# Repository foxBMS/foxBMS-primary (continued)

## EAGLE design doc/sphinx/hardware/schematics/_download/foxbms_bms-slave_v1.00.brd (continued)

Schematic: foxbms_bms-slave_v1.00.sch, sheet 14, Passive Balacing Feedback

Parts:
C1401, C1402: 1uF, 20%, 16V; 0603
IC1401, IC1402, IC1403, IC1404, IC1405, IC1406, IC1407, IC1408, IC1409, IC1410, IC1411, IC1412: CPC1008N; K_SMD_SOP-4_R_IXYS_REV01
M1401, M1402: LTC1380CGN; IC_SMD_SSOP-16_(GN16)_R_LINEAR_REV01
R1401, R1402, R1403, R1404, R1405, R1406, R1408, R1409, R1410, R1411, R1412, R1413: 130, 10%, 1/10W; 0603
R1407: 1k, 10%, 1/10W; 0603
R1414, R1415, R1416, R1417, R1418, R1419, R1420, R1421, R1422, R1423, R1424, R1425, R1426, R1427, R1428, R1429: 10k, 10%, 1/10W; 0603

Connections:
+5.0V_VREG_1: C1401.2, C1402.2, M1401.12 (A1), M1401.16 (VCC), M1402.12 (A1), M1402.13 (A0), M1402.16 (VCC), R1407.1; also elsewhere on the board
CELL0_FEEDBACK: IC1406.3, M1401.1 (S0), R1414.1
CELL0_FEEDBACK+: R1406.2; also elsewhere on the board
CELL1_FEEDBACK: IC1405.3, M1401.2 (S1), R1415.1
CELL1_FEEDBACK+: R1405.2; also elsewhere on the board
CELL2_FEEDBACK: IC1404.3, M1401.3 (S2), R1416.1
CELL2_FEEDBACK+: R1404.2; also elsewhere on the board
CELL3_FEEDBACK: IC1403.3, M1401.4 (S3), R1417.1
CELL3_FEEDBACK+: R1403.2; also elsewhere on the board
CELL4_FEEDBACK: IC1402.3, M1401.5 (S4), R1418.1
CELL4_FEEDBACK+: R1402.2; also elsewhere on the board
CELL5_FEEDBACK: IC1401.3, M1401.6 (S5), R1419.1
CELL5_FEEDBACK+: R1401.2; also elsewhere on the board
CELL6_FEEDBACK: IC1412.3, M1401.7 (S6), R1420.1
CELL6_FEEDBACK+: R1413.2; also elsewhere on the board
CELL7_FEEDBACK: IC1411.3, M1401.8 (S7), R1421.1
CELL7_FEEDBACK+: R1412.2; also elsewhere on the board
CELL8_FEEDBACK: IC1410.3, M1402.1 (S0), R1422.1
CELL8_FEEDBACK+: R1411.2; also elsewhere on the board
CELL9_FEEDBACK: IC1409.3, M1402.2 (S1), R1423.1
CELL9_FEEDBACK+: R1410.2; also elsewhere on the board
CELL10_FEEDBACK: IC1408.3, M1402.3 (S2), R1424.1
CELL10_FEEDBACK+: R1409.2; also elsewhere on the board
CELL11_FEEDBACK: IC1407.3, M1402.4 (S3), R1425.1
CELL11_FEEDBACK+: R1408.2; also elsewhere on the board
FUSED_CELL_0+: IC1405.2 (CON-); also elsewhere on the board
FUSED_CELL_1+: IC1404.2 (CON-); also elsewhere on the board
FUSED_CELL_2+: IC1403.2 (CON-); also elsewhere on the board
FUSED_CELL_3+: IC1402.2 (CON-); also elsewhere on the board
FUSED_CELL_4+: IC1401.2 (CON-); also elsewhere on the board
FUSED_CELL_5+: IC1412.2 (CON-); also elsewhere on the board
FUSED_CELL_6+: IC1411.2 (CON-); also elsewhere on the board
FUSED_CELL_7+: IC1410.2 (CON-); also elsewhere on the board
FUSED_CELL_8+: IC1409.2 (CON-); also elsewhere on the board
FUSED_CELL_9+: IC1408.2 (CON-); also elsewhere on the board
FUSED_CELL_10+: IC1407.2 (CON-); also elsewhere on the board
FUSED_VBAT-: C1401.1, C1402.1, IC1406.2 (CON-), M1401.10 (VEE), M1401.11 (GND), M1401.13 (A0), M1402.10 (VEE), M1402.11 (GND), R1414.2, R1415.2, R1416.2, R1417.2, R1418.2, R1419.2, R1420.2, R1421.2, R1422.2, R1423.2, R1424.2, R1425.2, R1426.2, R1427.2, R1428.2, R1429.2; also elsewhere on the board
unnamed: IC1401.4, IC1402.4, IC1403.4, IC1404.4, IC1405.4, IC1406.4, IC1407.4, IC1408.4, IC1409.4, IC1410.4, IC1411.4, IC1412.4, R1407.2
unnamed: IC1402.1 (CON+), R1402.1
unnamed: IC1403.1 (CON+), R1403.1
unnamed: IC1404.1 (CON+), R1404.1
unnamed: IC1408.1 (CON+), R1409.1
unnamed: IC1409.1 (CON+), R1410.1
unnamed: IC1405.1 (CON+), R1405.1
unnamed: IC1407.1 (CON+), R1408.1
unnamed: IC1410.1 (CON+), R1411.1
unnamed: IC1411.1 (CON+), R1412.1
unnamed: IC1406.1 (CON+), R1406.1
unnamed: IC1412.1 (CON+), R1413.1
unnamed: IC1401.1 (CON+), R1401.1
SECONDARY-OPA_IN: M1401.9 (DO), M1402.9 (DO); also elsewhere on the board
SECONDARY-SCL: M1401.15 (SCL), M1402.15 (SCL); also elsewhere on the board
SECONDARY-SDA: M1401.14 (SDA), M1402.14 (SDA); also elsewhere on the board
SECONDARY_D/A_INPUT_0: M1402.5 (S4), R1426.1; also elsewhere on the board
SECONDARY_D/A_INPUT_1: M1402.6 (S5), R1427.1; also elsewhere on the board
SECONDARY_D/A_INPUT_2: M1402.7 (S6), R1428.1; also elsewhere on the board
SECONDARY_D/A_INPUT_3: M1402.8 (S7), R1429.1; also elsewhere on the board

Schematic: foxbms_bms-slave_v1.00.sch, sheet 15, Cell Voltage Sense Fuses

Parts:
F1501, F1515: 0.5A, 63V, 0.25R; 1206
F1502, F1503, F1504, F1505, F1506, F1507, F1508, F1509, F1510, F1511, F1512, F1513, F1514: FUSE: 0.250A, 32V, 0.57R; 0603
LSP1501, LSP1502, LSP1503, LSP1504, LSP1505, LSP1506, LSP1507, LSP1508, LSP1509, LSP1510, LSP1511, LSP1512, LSP1513, LSP1514, LSP1515: PAD_2.0X1.5MM; PAD2.0X1.5MM
SJ1501, SJ1502: SJ

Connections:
CELL_0+: F1503.1; also elsewhere on the board
CELL_0-: F1502.1, SJ1501.1; also elsewhere on the board
CELL_1+: F1504.1; also elsewhere on the board
CELL_2+: F1505.1; also elsewhere on the board
CELL_3+: F1506.1; also elsewhere on the board
CELL_4+: F1507.1; also elsewhere on the board
CELL_5+: F1508.1; also elsewhere on the board
CELL_6+: F1509.1; also elsewhere on the board
CELL_7+: F1510.1; also elsewhere on the board
CELL_8+: F1511.1; also elsewhere on the board
CELL_9+: F1512.1; also elsewhere on the board
CELL_10+: F1513.1; also elsewhere on the board
CELL_11+: F1514.1, SJ1502.2; also elsewhere on the board
FUSED_CELL_0+: F1503.2, LSP1503.P$1; also elsewhere on the board
FUSED_CELL_0-: F1502.2, LSP1502.P$1; also elsewhere on the board
FUSED_CELL_1+: F1504.2, LSP1504.P$1; also elsewhere on the board
FUSED_CELL_2+: F1505.2, LSP1505.P$1; also elsewhere on the board
FUSED_CELL_3+: F1506.2, LSP1506.P$1; also elsewhere on the board
FUSED_CELL_4+: F1507.2, LSP1507.P$1; also elsewhere on the board
FUSED_CELL_5+: F1508.2, LSP1508.P$1; also elsewhere on the board
FUSED_CELL_6+: F1509.2, LSP1509.P$1; also elsewhere on the board
FUSED_CELL_7+: F1510.2, LSP1510.P$1; also elsewhere on the board
FUSED_CELL_8+: F1511.2, LSP1511.P$1; also elsewhere on the board
FUSED_CELL_9+: F1512.2, LSP1512.P$1; also elsewhere on the board
FUSED_CELL_10+: F1513.2, LSP1513.P$1; also elsewhere on the board
FUSED_CELL_11+: F1514.2, LSP1514.P$1; also elsewhere on the board
FUSED_VBAT+: F1515.2, LSP1515.P$1; also elsewhere on the board
FUSED_VBAT-: F1501.2, LSP1501.P$1; also elsewhere on the board
VBAT+: F1515.1, SJ1502.1; also elsewhere on the board
VBAT-: F1501.1, SJ1501.2; also elsewhere on the board

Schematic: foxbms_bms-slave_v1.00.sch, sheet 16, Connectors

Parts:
X1601, X1602: 43045-0406_MOLEX_4PIN; X_SMD_MOLEX_43045-0408_R_REV01
X1603: 43045-1606_MOLEX_16PIN; X_SMD_MOLEX_43045-1608_R_REV01
X1604, X1607, X1608: MA10-2
X1605: MA09-2
X1606: 43045-2406_MOLEX_24PIN; X_SMD_MOLEX_43045-2408_R_REV01

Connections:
+3.0V_VREF2_0: X1604.18; also elsewhere on the board
+3.0V_VREF2_1: X1604.17; also elsewhere on the board
+5.0V_VREG_0: X1604.16; also elsewhere on the board
+5.0V_VREG_1: X1604.15; also elsewhere on the board
CELL_0+: X1603.2; also elsewhere on the board
CELL_0-: X1603.9; also elsewhere on the board
CELL_1+: X1603.10; also elsewhere on the board
CELL_2+: X1603.3; also elsewhere on the board
CELL_3+: X1603.11; also elsewhere on the board
CELL_4+: X1603.4; also elsewhere on the board
CELL_5+: X1603.12; also elsewhere on the board
CELL_6+: X1603.5; also elsewhere on the board
CELL_7+: X1603.13; also elsewhere on the board
CELL_8+: X1603.6; also elsewhere on the board
CELL_9+: X1603.14; also elsewhere on the board
CELL_10+: X1603.7; also elsewhere on the board
CELL_11+: X1603.15; also elsewhere on the board
FUSED_VBAT-: X1605.17, X1605.18, X1606.1, X1606.2, X1606.3, X1606.4, X1606.5, X1606.6, X1606.7, X1606.8, X1606.9, X1606.10, X1606.11, X1606.12, X1607.2, X1607.4, X1607.6, X1607.8, X1607.10, X1607.12, X1607.14, X1607.16, X1607.18, X1607.20, X1608.2, X1608.4, X1608.6, X1608.8, X1608.10, X1608.12, X1608.14, X1608.16, X1608.18, X1608.20; also elsewhere on the board
PRIMARY-GPIO0-OPT: X1604.6; also elsewhere on the board
PRIMARY-GPIO1: X1604.8; also elsewhere on the board
PRIMARY-GPIO2: X1604.10; also elsewhere on the board
PRIMARY-GPIO3-OPT: X1604.12; also elsewhere on the board
PRIMARY-GPIO4-OPT: X1604.14; also elsewhere on the board
PRIMARY-IN+_P: X1601.1; also elsewhere on the board
PRIMARY-IN-_N: X1601.3; also elsewhere on the board
PRIMARY-OUT+_P: X1601.4; also elsewhere on the board
PRIMARY-OUT-_N: X1601.2; also elsewhere on the board
PRIMARY-WDT: X1604.20; also elsewhere on the board
PRIMARY_D/A_INPUT_0: X1605.1; also elsewhere on the board
PRIMARY_D/A_INPUT_1: X1605.2; also elsewhere on the board
PRIMARY_D/A_INPUT_2: X1605.3; also elsewhere on the board
PRIMARY_D/A_INPUT_3: X1605.4; also elsewhere on the board
PRIMARY_D/A_INPUT_4: X1605.5; also elsewhere on the board
PRIMARY_D/A_INPUT_5: X1605.6; also elsewhere on the board
PRIMARY_D/A_INPUT_6: X1605.7; also elsewhere on the board
PRIMARY_D/A_INPUT_7: X1605.8; also elsewhere on the board
PRIMARY_D/A_INPUT_8: X1605.9; also elsewhere on the board
PRIMARY_D/A_INPUT_9: X1605.10; also elsewhere on the board
PRIMARY_D/A_INPUT_10: X1605.11; also elsewhere on the board
PRIMARY_D/A_INPUT_11: X1605.12; also elsewhere on the board
PRIMARY_D/A_INPUT_12: X1605.13; also elsewhere on the board
PRIMARY_D/A_INPUT_13: X1605.14; also elsewhere on the board
PRIMARY_D/A_INPUT_14: X1605.15; also elsewhere on the board
PRIMARY_D/A_INPUT_15: X1605.16; also elsewhere on the board
SECONDARY-GPIO0-OPT: X1604.5; also elsewhere on the board
SECONDARY-GPIO1: X1604.7; also elsewhere on the board
SECONDARY-GPIO2: X1604.9; also elsewhere on the board
SECONDARY-GPIO3-OPT: X1604.11; also elsewhere on the board
SECONDARY-GPIO4-OPT: X1604.13; also elsewhere on the board
SECONDARY-IN+_P: X1602.1; also elsewhere on the board
SECONDARY-IN-_N: X1602.3; also elsewhere on the board
SECONDARY-OUT+_P: X1602.4; also elsewhere on the board
SECONDARY-OUT-_N: X1602.2; also elsewhere on the board
SECONDARY-WDT: X1604.19; also elsewhere on the board
SECONDARY_D/A_INPUT_0: X1604.1; also elsewhere on the board
SECONDARY_D/A_INPUT_1: X1604.2; also elsewhere on the board
SECONDARY_D/A_INPUT_2: X1604.3; also elsewhere on the board
SECONDARY_D/A_INPUT_3: X1604.4; also elsewhere on the board
T-SENSOR_0: X1606.24; also elsewhere on the board
T-SENSOR_1: X1606.23; also elsewhere on the board
T-SENSOR_2: X1606.22; also elsewhere on the board
T-SENSOR_3: X1606.21; also elsewhere on the board
T-SENSOR_4: X1606.20; also elsewhere on the board
T-SENSOR_5: X1606.19; also elsewhere on the board
T-SENSOR_6: X1607.1; also elsewhere on the board
T-SENSOR_7: X1607.3; also elsewhere on the board
T-SENSOR_8: X1607.5; also elsewhere on the board
T-SENSOR_9: X1607.7; also elsewhere on the board
T-SENSOR_10: X1607.9; also elsewhere on the board
T-SENSOR_11: X1607.11; also elsewhere on the board
T-SENSOR_12: X1607.13; also elsewhere on the board
T-SENSOR_13: X1607.15; also elsewhere on the board
T-SENSOR_14: X1607.17; also elsewhere on the board
T-SENSOR_15: X1607.19; also elsewhere on the board
T-SENSOR_16: X1606.18; also elsewhere on the board
T-SENSOR_17: X1606.17; also elsewhere on the board
T-SENSOR_18: X1606.16; also elsewhere on the board
T-SENSOR_19: X1606.15; also elsewhere on the board
T-SENSOR_20: X1606.14; also elsewhere on the board
T-SENSOR_21: X1606.13; also elsewhere on the board
T-SENSOR_22: X1608.19; also elsewhere on the board
T-SENSOR_23: X1608.17; also elsewhere on the board
T-SENSOR_24: X1608.15; also elsewhere on the board
T-SENSOR_25: X1608.13; also elsewhere on the board
T-SENSOR_26: X1608.11; also elsewhere on the board
T-SENSOR_27: X1608.9; also elsewhere on the board
T-SENSOR_28: X1608.7; also elsewhere on the board
T-SENSOR_29: X1608.5; also elsewhere on the board
T-SENSOR_30: X1608.3; also elsewhere on the board
T-SENSOR_31: X1608.1; also elsewhere on the board
VBAT+: X1603.16; also elsewhere on the board
VBAT-: X1603.1; also elsewhere on the board

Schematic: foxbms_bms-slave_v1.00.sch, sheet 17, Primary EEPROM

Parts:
C1701: 100nF, 20%, 16V; 0603
IC1701: 24AA02UID; IC_SMD_SOT23-5_R_MICROCHIP_REV01

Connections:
+5.0V_VREG_0: C1701.2, IC1701.4 (VCC); also elsewhere on the board
FUSED_VBAT-: C1701.1, IC1701.2 (VSS); also elsewhere on the board
PRIMARY-SCL: IC1701.1 (SCL); also elsewhere on the board
PRIMARY-SDA: IC1701.3 (SDA); also elsewhere on the board

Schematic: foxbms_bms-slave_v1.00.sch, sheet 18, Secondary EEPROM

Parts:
C1801: 100nF, 20%, 16V; 0603
IC1801: 24AA02UID; IC_SMD_SOT23-5_R_MICROCHIP_REV01

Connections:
+5.0V_VREG_1: C1801.2, IC1801.4 (VCC); also elsewhere on the board
FUSED_VBAT-: C1801.1, IC1801.2 (VSS); also elsewhere on the board
SECONDARY-SCL: IC1801.1 (SCL); also elsewhere on the board
SECONDARY-SDA: IC1801.3 (SDA); also elsewhere on the board

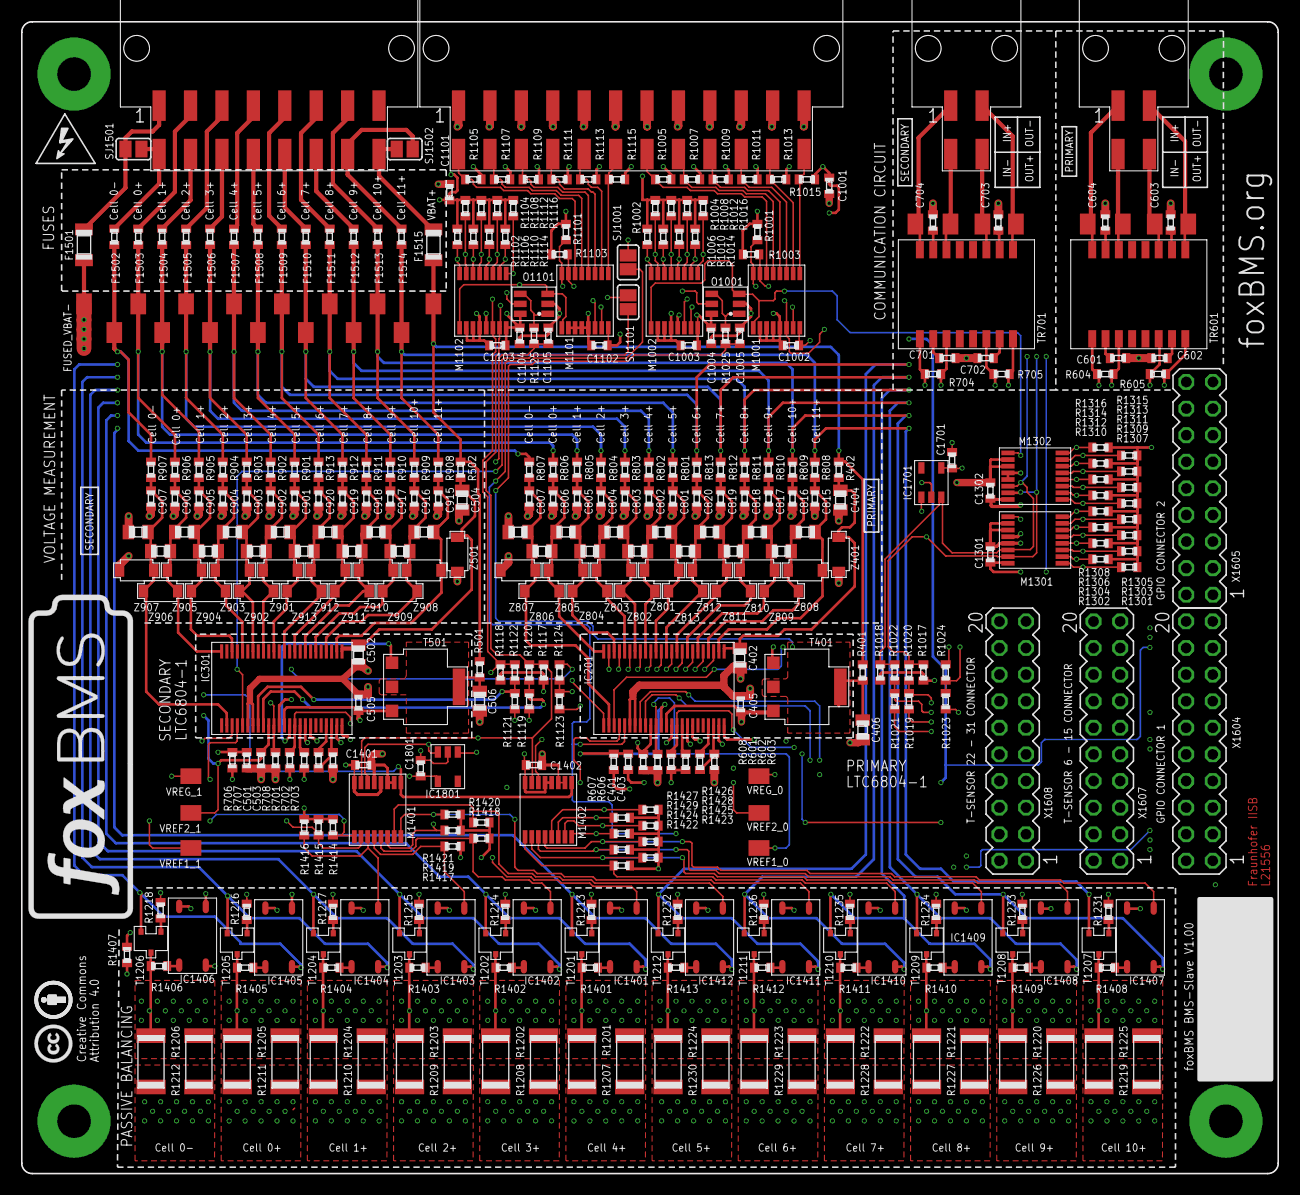
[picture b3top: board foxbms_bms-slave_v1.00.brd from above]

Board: 6 copper layers, 120.0 x 110.0 mm, 391 parts (0 on the bottom side), 244 nets.

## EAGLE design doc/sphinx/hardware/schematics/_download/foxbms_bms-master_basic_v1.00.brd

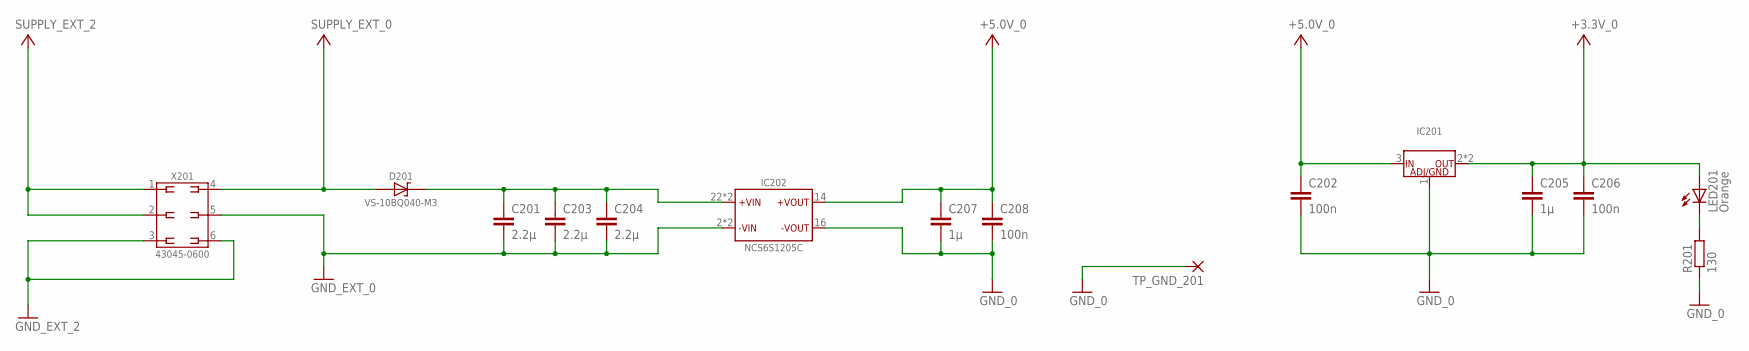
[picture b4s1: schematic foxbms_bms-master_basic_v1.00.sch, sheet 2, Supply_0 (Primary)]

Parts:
C201, C203, C204: 2.2µ; C0805
C202, C206, C208: 100n; C0603
C205, C207: 1µ; C0603
D201: VS-10BQ040-M3; D_SMD_SMB_(DO-214AA)_R_VISHAY_REV01
IC201: LM1085IS-5.0/NOPB; IC_SMD_TO-263-3_(KTT0003B)_R_TI_REV01
IC202: MURATA_NCS6S1205C; IC_TH_32,00MMX20,00MMX10,00MM_(7-PIN)_R_MURATA_REV01
LED201: Orange; CHIP-LED0603
R201: 130; R0603
TP_GND_201: 1,6/0,8
X201: 43045-0600_MOLEX_6PIN; X_TH_MOLEX_43045-0600_R_REV01

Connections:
+3.3V_0: C205.1, C206.1, IC201.2 (OUT), IC201.4 (OUT), LED201.A; also elsewhere on the board
+5.0V_0: C202.1, C207.1, C208.1, IC201.3 (IN), IC202.14 (+VOUT); also elsewhere on the board
GND_0: C202.2, C205.2, C206.2, C207.2, C208.2, IC201.1 (ADJ/GND), IC202.16 (-VOUT), R201.1, TP_GND_201.1; also elsewhere on the board
GND_EXT_0: C201.2, C203.2, C204.2, IC202.2 (-VIN), IC202.3 (-VIN), X201.5; also elsewhere on the board
GND_EXT_2: X201.3, X201.6; also elsewhere on the board
unnamed: LED201.C, R201.2
unnamed: C201.1, C203.1, C204.1, D201.C, IC202.22 (+VIN), IC202.23 (+VIN)
SUPPLY_EXT_0: D201.A, X201.4; also elsewhere on the board
SUPPLY_EXT_2: X201.1, X201.2; also elsewhere on the board

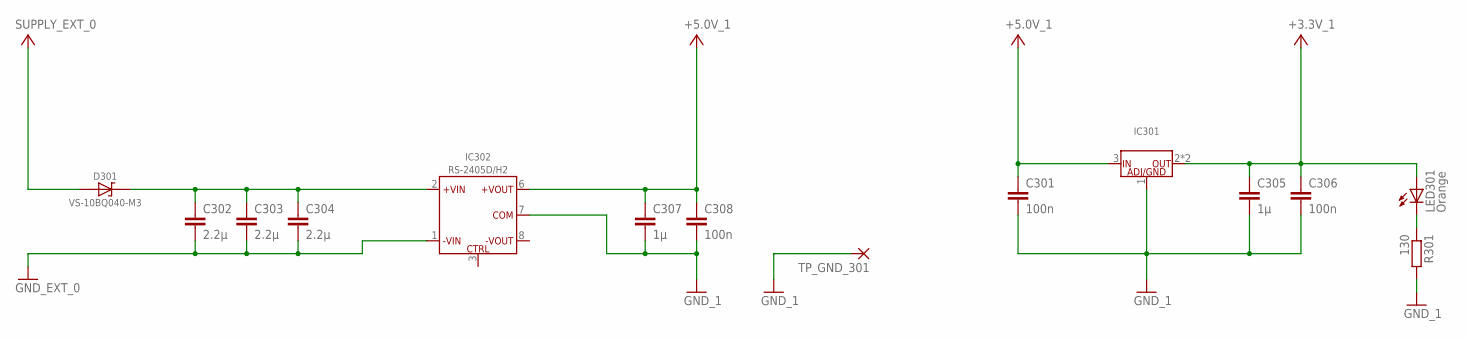
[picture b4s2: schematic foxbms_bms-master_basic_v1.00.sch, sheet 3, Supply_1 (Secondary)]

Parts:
C301, C306, C308: 100n; C0603
C302, C303, C304: 2.2µ; C0805
C305, C307: 1µ; C0603
D301: VS-10BQ040-M3; D_SMD_SMB_(DO-214AA)_R_VISHAY_REV01
IC301: LM1085IS-5.0/NOPB; IC_SMD_TO-263-3_(KTT0003B)_R_TI_REV01
IC302: RS-2405D/H2; IC_TH_SIP8_R_RECOM_REV01
LED301: Orange; CHIP-LED0603
R301: 130; R0603
TP_GND_301: 1,6/0,8

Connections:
+3.3V_1: C305.1, C306.1, IC301.2 (OUT), IC301.4 (OUT), LED301.A; also elsewhere on the board
+5.0V_1: C301.1, C307.1, C308.1, IC301.3 (IN), IC302.6 (+VOUT); also elsewhere on the board
GND_1: C301.2, C305.2, C306.2, C307.2, C308.2, IC301.1 (ADJ/GND), IC302.7 (COM), R301.2, TP_GND_301.1; also elsewhere on the board
GND_EXT_0: C302.2, C303.2, C304.2, IC302.1 (-VIN); also elsewhere on the board
unnamed: LED301.C, R301.1
unnamed: C302.1, C303.1, C304.1, D301.C, IC302.2 (+VIN)
SUPPLY_EXT_0: D301.A; also elsewhere on the board

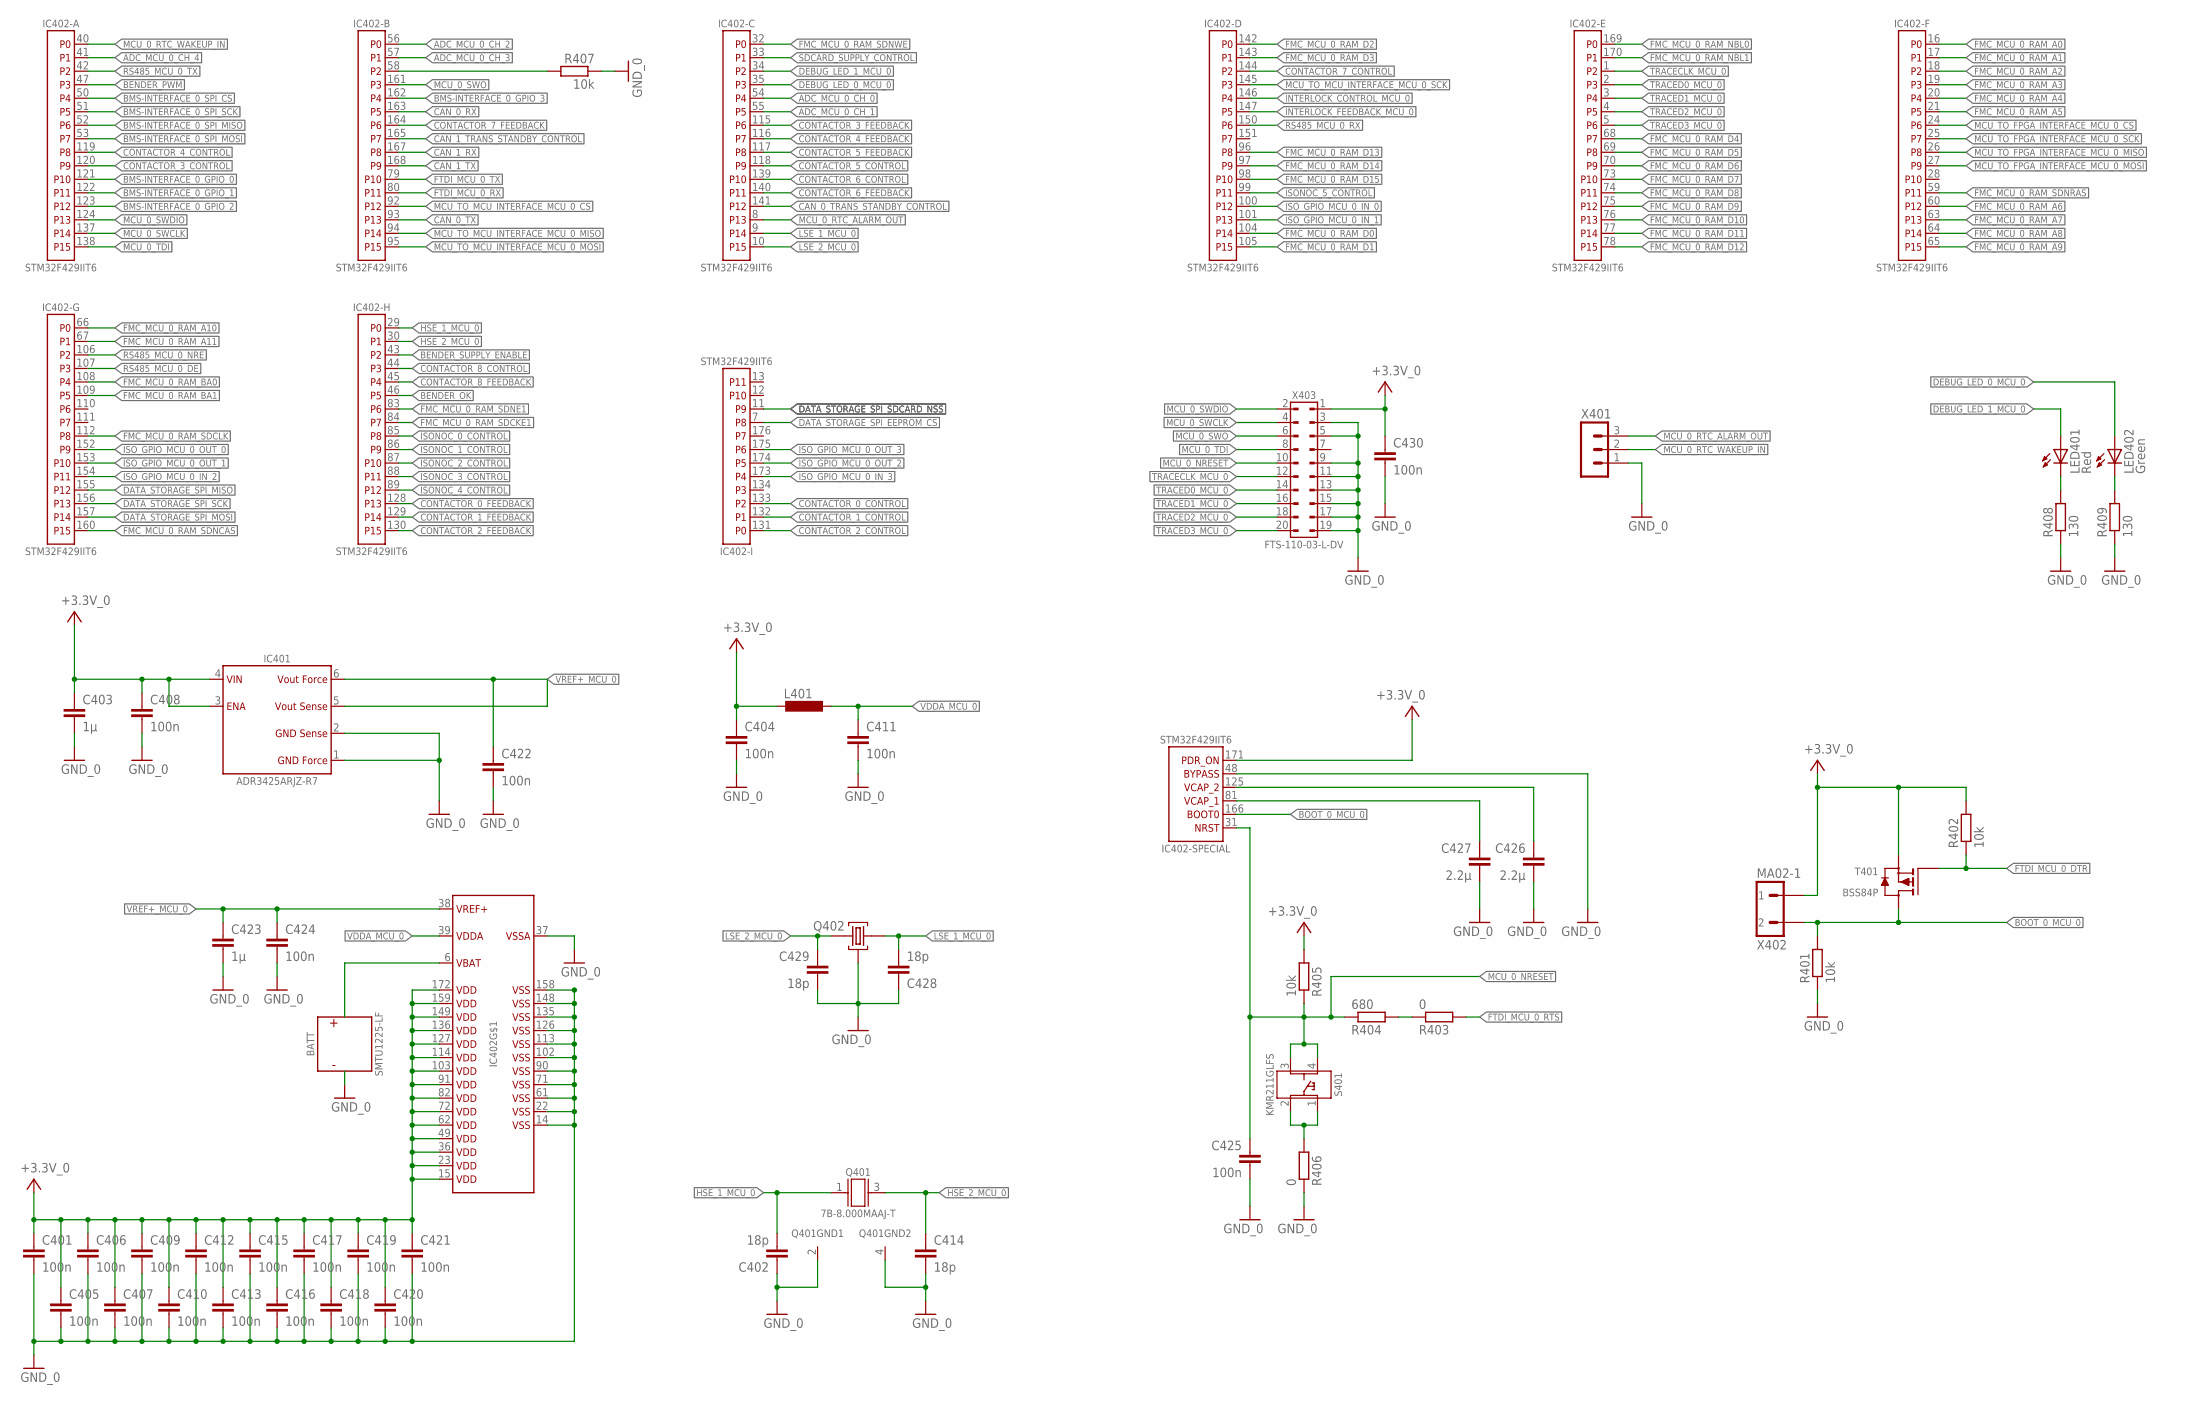
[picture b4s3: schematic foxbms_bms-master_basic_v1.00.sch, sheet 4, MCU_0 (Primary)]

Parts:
BATT: SMTU1225-LF; X_SMD_(23,70MM_X_12,70MM_X_5,00MM)_R_RENATA_REV01
C401, C404, C405, C406, C407, C408, C409, C410, C411, C412, C413, C415, C416, C417, C418, C419, C420, C421, C422, C424, C425, C430: 100n; C0603
C402, C414, C428, C429: 18p; C0603
C403, C423: 1µ; C0603
C426, C427: 2.2µ; C0603
IC401: ADR3425ARJZ; IC_SMD_SOT23-6_(MO-178-AB)_R_AD_REV01
IC402: STM32F429IIT6; IC_SMD_LQFP176_R_ST_REV01
L401: L0805; 0805
LED401: Red; CHIP-LED0603
LED402: Green; CHIP-LED0603
Q401: 7B-8.000MAAJ-T; G_SMD_5,00MM_X_3,20MM_0,90MM_(7B)_TXC_REV01
Q402: MS3V; MS3V-T1R
R401, R402, R405, R407: 10k; R0603
R403, R406: 0; R0603
R404: 680; R0603
R408, R409: 130; R0603
S401: KMR211GLFS; S_SMD_4,60MMX2,80MMX1,90MM_R_CK-COMPONENTS_REV01
T401: BSS84P; V_SMD_SOT23_(TO-236AB)_R_INFINEON_REV01
X401: MA03-1
X402: MA02-1
X403: SAMTEC_FTS_20POL_HEADER_VERTIKAL_REV01; X_SMD_FTS_110-03_(20POL)_R_SAMTEC_REV01

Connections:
+3.3V_0: C401.1, C403.1, C404.1, C405.1, C406.1, C407.1, C408.1, C409.1, C410.1, C412.1, C413.1, C415.1, C416.1, C417.1, C418.1, C419.1, C420.1, C421.1, C430.1, IC401.3 (ENABLE), IC401.4 (VIN), IC402.15 (VDD1), IC402.23 (VDD2), IC402.36 (VDD3), IC402.49 (VDD4), IC402.62 (VDD5), IC402.72 (VDD6), IC402.82 (VDD7), IC402.91 (VDD8), IC402.103 (VDD9), IC402.114 (VDD10), IC402.127 (VDD11), IC402.136 (VDD12), IC402.149 (VDD13), IC402.159 (VDD14), IC402.171 (PDR_ON), IC402.172 (VDD15), L401.1, R402.2, R405.2, T401.2 (S), X402.1, X403.1; also elsewhere on the board
ADC_MCU_0_CH_0: IC402.54 (P4); also elsewhere on the board
ADC_MCU_0_CH_1: IC402.55 (P5); also elsewhere on the board
ADC_MCU_0_CH_2: IC402.56 (P0); also elsewhere on the board
ADC_MCU_0_CH_3: IC402.57 (P1); also elsewhere on the board
ADC_MCU_0_CH_4: IC402.41 (P1); also elsewhere on the board
BENDER_OK: IC402.46 (P5); also elsewhere on the board
BENDER_PWM: IC402.47 (P3); also elsewhere on the board
BENDER_SUPPLY_ENABLE: IC402.43 (P2); also elsewhere on the board
BMS-INTERFACE_0_GPIO_0: IC402.121 (P10); also elsewhere on the board
BMS-INTERFACE_0_GPIO_1: IC402.122 (P11); also elsewhere on the board
BMS-INTERFACE_0_GPIO_2: IC402.123 (P12); also elsewhere on the board
BMS-INTERFACE_0_GPIO_3: IC402.162 (P4); also elsewhere on the board
BMS-INTERFACE_0_SPI_CS: IC402.50 (P4); also elsewhere on the board
BMS-INTERFACE_0_SPI_MISO: IC402.52 (P6); also elsewhere on the board
BMS-INTERFACE_0_SPI_MOSI: IC402.53 (P7); also elsewhere on the board
BMS-INTERFACE_0_SPI_SCK: IC402.51 (P5); also elsewhere on the board
BOOT_0_MCU_0: IC402.166 (BOOT0), R401.2, T401.3 (D), X402.2
CAN_0_RX: IC402.163 (P5); also elsewhere on the board
CAN_0_TRANS_STANDBY_CONTROL: IC402.141 (P12); also elsewhere on the board
CAN_0_TX: IC402.93 (P13); also elsewhere on the board
CAN_1_RX: IC402.167 (P8); also elsewhere on the board
CAN_1_TRANS_STANDBY_CONTROL: IC402.165 (P7); also elsewhere on the board
CAN_1_TX: IC402.168 (P9); also elsewhere on the board
CONTACTOR_0_CONTROL: IC402.133 (P2); also elsewhere on the board
CONTACTOR_0_FEEDBACK: IC402.128 (P13); also elsewhere on the board
CONTACTOR_1_CONTROL: IC402.132 (P1); also elsewhere on the board
CONTACTOR_1_FEEDBACK: IC402.129 (P14); also elsewhere on the board
CONTACTOR_2_CONTROL: IC402.131 (P0); also elsewhere on the board
CONTACTOR_2_FEEDBACK: IC402.130 (P15); also elsewhere on the board
CONTACTOR_3_CONTROL: IC402.120 (P9); also elsewhere on the board
CONTACTOR_3_FEEDBACK: IC402.115 (P6); also elsewhere on the board
CONTACTOR_4_CONTROL: IC402.119 (P8); also elsewhere on the board
CONTACTOR_4_FEEDBACK: IC402.116 (P7); also elsewhere on the board
CONTACTOR_5_CONTROL: IC402.118 (P9); also elsewhere on the board
CONTACTOR_5_FEEDBACK: IC402.117 (P8); also elsewhere on the board
CONTACTOR_6_CONTROL: IC402.139 (P10); also elsewhere on the board
CONTACTOR_6_FEEDBACK: IC402.140 (P11); also elsewhere on the board
CONTACTOR_7_CONTROL: IC402.144 (P2); also elsewhere on the board
CONTACTOR_7_FEEDBACK: IC402.164 (P6); also elsewhere on the board
CONTACTOR_8_CONTROL: IC402.44 (P3); also elsewhere on the board
CONTACTOR_8_FEEDBACK: IC402.45 (P4); also elsewhere on the board
DATA_STORAGE_SPI_EEPROM_CS: IC402.7 (P8); also elsewhere on the board
DATA_STORAGE_SPI_MISO: IC402.155 (P12); also elsewhere on the board
DATA_STORAGE_SPI_MOSI: IC402.157 (P14); also elsewhere on the board
DATA_STORAGE_SPI_SCK: IC402.156 (P13); also elsewhere on the board
DATA_STORAGE_SPI_SDCARD_NSS: IC402.11 (P9); also elsewhere on the board
DEBUG_LED_0_MCU_0: IC402.35 (P3), LED402.A
DEBUG_LED_1_MCU_0: IC402.34 (P2), LED401.A
FMC_MCU_0_RAM_A0: IC402.16 (P0); also elsewhere on the board
FMC_MCU_0_RAM_A1: IC402.17 (P1); also elsewhere on the board
FMC_MCU_0_RAM_A2: IC402.18 (P2); also elsewhere on the board
FMC_MCU_0_RAM_A3: IC402.19 (P3); also elsewhere on the board
FMC_MCU_0_RAM_A4: IC402.20 (P4); also elsewhere on the board
FMC_MCU_0_RAM_A5: IC402.21 (P5); also elsewhere on the board
FMC_MCU_0_RAM_A6: IC402.60 (P12); also elsewhere on the board
FMC_MCU_0_RAM_A7: IC402.63 (P13); also elsewhere on the board
FMC_MCU_0_RAM_A8: IC402.64 (P14); also elsewhere on the board
FMC_MCU_0_RAM_A9: IC402.65 (P15); also elsewhere on the board
FMC_MCU_0_RAM_A10: IC402.66 (P0); also elsewhere on the board
FMC_MCU_0_RAM_A11: IC402.67 (P1); also elsewhere on the board
FMC_MCU_0_RAM_BA0: IC402.108 (P4); also elsewhere on the board
FMC_MCU_0_RAM_BA1: IC402.109 (P5); also elsewhere on the board
FMC_MCU_0_RAM_D0: IC402.104 (P14); also elsewhere on the board
FMC_MCU_0_RAM_D1: IC402.105 (P15); also elsewhere on the board
FMC_MCU_0_RAM_D2: IC402.142 (P0); also elsewhere on the board
FMC_MCU_0_RAM_D3: IC402.143 (P1); also elsewhere on the board
FMC_MCU_0_RAM_D4: IC402.68 (P7); also elsewhere on the board
FMC_MCU_0_RAM_D5: IC402.69 (P8); also elsewhere on the board
FMC_MCU_0_RAM_D6: IC402.70 (P9); also elsewhere on the board
FMC_MCU_0_RAM_D7: IC402.73 (P10); also elsewhere on the board
FMC_MCU_0_RAM_D8: IC402.74 (P11); also elsewhere on the board
FMC_MCU_0_RAM_D9: IC402.75 (P12); also elsewhere on the board
FMC_MCU_0_RAM_D10: IC402.76 (P13); also elsewhere on the board
FMC_MCU_0_RAM_D11: IC402.77 (P14); also elsewhere on the board
FMC_MCU_0_RAM_D12: IC402.78 (P15); also elsewhere on the board
FMC_MCU_0_RAM_D13: IC402.96 (P8); also elsewhere on the board
FMC_MCU_0_RAM_D14: IC402.97 (P9); also elsewhere on the board
FMC_MCU_0_RAM_D15: IC402.98 (P10); also elsewhere on the board
FMC_MCU_0_RAM_NBL0: IC402.169 (P0); also elsewhere on the board
FMC_MCU_0_RAM_NBL1: IC402.170 (P1); also elsewhere on the board
FMC_MCU_0_RAM_SDCKE1: IC402.84 (P7); also elsewhere on the board
FMC_MCU_0_RAM_SDCLK: IC402.112 (P8); also elsewhere on the board
FMC_MCU_0_RAM_SDNCAS: IC402.160 (P15); also elsewhere on the board
FMC_MCU_0_RAM_SDNE1: IC402.83 (P6); also elsewhere on the board
FMC_MCU_0_RAM_SDNRAS: IC402.59 (P11); also elsewhere on the board
FMC_MCU_0_RAM_SDNWE: IC402.32 (P0); also elsewhere on the board
FTDI_MCU_0_DTR: R402.1, T401.1 (G); also elsewhere on the board
FTDI_MCU_0_RTS: R403.2; also elsewhere on the board
FTDI_MCU_0_RX: IC402.80 (P11); also elsewhere on the board
FTDI_MCU_0_TX: IC402.79 (P10); also elsewhere on the board
GND_0: BATT.-, C401.2, C402.1, C403.2, C404.2, C405.2, C406.2, C407.2, C408.2, C409.2, C410.2, C411.2, C412.2, C413.2, C414.2, C415.2, C416.2, C417.2, C418.2, C419.2, C420.2, C421.2, C422.2, C423.2, C424.2, C425.2, C426.2, C427.2, C428.1, C429.2, C430.2, IC401.1 (GND_FORCE), IC401.2 (GND_SENSE), IC402.14 (VSS1), IC402.22 (VSS2), IC402.37 (VSSA), IC402.48 (BYPASS_REG), IC402.61 (VSS3), IC402.71 (VSS4), IC402.90 (VSS5), IC402.102 (VSS6), IC402.113 (VSS7), IC402.126 (VSS8), IC402.135 (VSS9), IC402.148 (VSS10), IC402.158 (VSS11), Q401.2 (GND), Q401.4 (GND), Q402.P$3 (2), R401.1, R406.1, R407.1, R408.1, R409.1, X401.1, X403.3, X403.5, X403.9, X403.11, X403.13, X403.15, X403.17, X403.19; also elsewhere on the board
HSE_1_MCU_0: C402.2, IC402.29 (P0), Q401.1 (A)
HSE_2_MCU_0: C414.1, IC402.30 (P1), Q401.3 (B)
INTERLOCK_CONTROL_MCU_0: IC402.146 (P4); also elsewhere on the board
INTERLOCK_FEEDBACK_MCU_0: IC402.147 (P5); also elsewhere on the board
ISONOC_0_CONTROL: IC402.85 (P8); also elsewhere on the board
ISONOC_1_CONTROL: IC402.86 (P9); also elsewhere on the board
ISONOC_2_CONTROL: IC402.87 (P10); also elsewhere on the board
ISONOC_3_CONTROL: IC402.88 (P11); also elsewhere on the board
ISONOC_4_CONTROL: IC402.89 (P12); also elsewhere on the board
ISONOC_5_CONTROL: IC402.99 (P11); also elsewhere on the board
ISO_GPIO_MCU_0_IN_0: IC402.100 (P12); also elsewhere on the board
ISO_GPIO_MCU_0_IN_1: IC402.101 (P13); also elsewhere on the board
ISO_GPIO_MCU_0_IN_2: IC402.154 (P11); also elsewhere on the board
ISO_GPIO_MCU_0_IN_3: IC402.173 (P4); also elsewhere on the board
ISO_GPIO_MCU_0_OUT_0: IC402.152 (P9); also elsewhere on the board
ISO_GPIO_MCU_0_OUT_1: IC402.153 (P10); also elsewhere on the board
ISO_GPIO_MCU_0_OUT_2: IC402.174 (P5); also elsewhere on the board
ISO_GPIO_MCU_0_OUT_3: IC402.175 (P6); also elsewhere on the board
LSE_1_MCU_0: C428.2, IC402.9 (P14), Q402.1
LSE_2_MCU_0: C429.1, IC402.10 (P15), Q402.2 (3)
MCU_0_NRESET: C425.1, IC402.31 (NRST), R404.1, R405.1, S401.3, S401.4, X403.10
MCU_0_RTC_ALARM_OUT: IC402.8 (P13), X401.3
MCU_0_RTC_WAKEUP_IN: IC402.40 (P0), X401.2
MCU_0_SWCLK: IC402.137 (P14), X403.4
MCU_0_SWDIO: IC402.124 (P13), X403.2
MCU_0_SWO: IC402.161 (P3), X403.6
MCU_0_TDI: IC402.138 (P15), X403.8
MCU_TO_FPGA_INTERFACE_MCU_0_CS: IC402.24 (P6); also elsewhere on the board
MCU_TO_FPGA_INTERFACE_MCU_0_MISO: IC402.26 (P8); also elsewhere on the board
MCU_TO_FPGA_INTERFACE_MCU_0_MOSI: IC402.27 (P9); also elsewhere on the board
MCU_TO_FPGA_INTERFACE_MCU_0_SCK: IC402.25 (P7); also elsewhere on the board
MCU_TO_MCU_INTERFACE_MCU_0_CS: IC402.92 (P12); also elsewhere on the board
MCU_TO_MCU_INTERFACE_MCU_0_MISO: IC402.94 (P14); also elsewhere on the board
MCU_TO_MCU_INTERFACE_MCU_0_MOSI: IC402.95 (P15); also elsewhere on the board
MCU_TO_MCU_INTERFACE_MCU_0_SCK: IC402.145 (P3); also elsewhere on the board
unnamed: C426.1, IC402.125 (VCAP_2)
unnamed: R406.2, S401.1, S401.2
unnamed: LED401.C, R408.2
unnamed: LED402.C, R409.2
unnamed: C427.1, IC402.81 (VCAP_1)
unnamed: IC402.58 (P2), R407.2
unnamed: R403.1, R404.2
unnamed: BATT.+, IC402.6 (VBAT)
RS485_MCU_0_DE: IC402.107 (P3); also elsewhere on the board
RS485_MCU_0_NRE: IC402.106 (P2); also elsewhere on the board
RS485_MCU_0_RX: IC402.150 (P6); also elsewhere on the board
RS485_MCU_0_TX: IC402.42 (P2); also elsewhere on the board
SDCARD_SUPPLY_CONTROL: IC402.33 (P1); also elsewhere on the board
TRACECLK_MCU_0: IC402.1 (P2), X403.12
TRACED0_MCU_0: IC402.2 (P3), X403.14
TRACED1_MCU_0: IC402.3 (P4), X403.16
TRACED2_MCU_0: IC402.4 (P5), X403.18
TRACED3_MCU_0: IC402.5 (P6), X403.20
VDDA_MCU_0: C411.1, IC402.39 (VDDA), L401.2
VREF+_MCU_0: C422.1, C423.1, C424.1, IC401.5 (VOUT_SENSE), IC401.6 (VOUT_FORCE), IC402.38 (VREF+)
